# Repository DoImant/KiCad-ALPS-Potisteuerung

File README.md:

# ALPS potentiometer control

Circuit for controlling an ALPS motor potentiometer with the help of an IR remote\
control. This circuit can be used to control the volume of an amplifier.

## Circuit diagram as PDF file

[Sheet](https://github.com/DoImant/Stuff/blob/main/ALPS-Drehpoti/ALPS-Potisteuerung.pdf)

## The PCB

## Software

The software for the Atmega88P can be found here: https://github.com/DoImant/ATmega88-ALPS-Motorpoti

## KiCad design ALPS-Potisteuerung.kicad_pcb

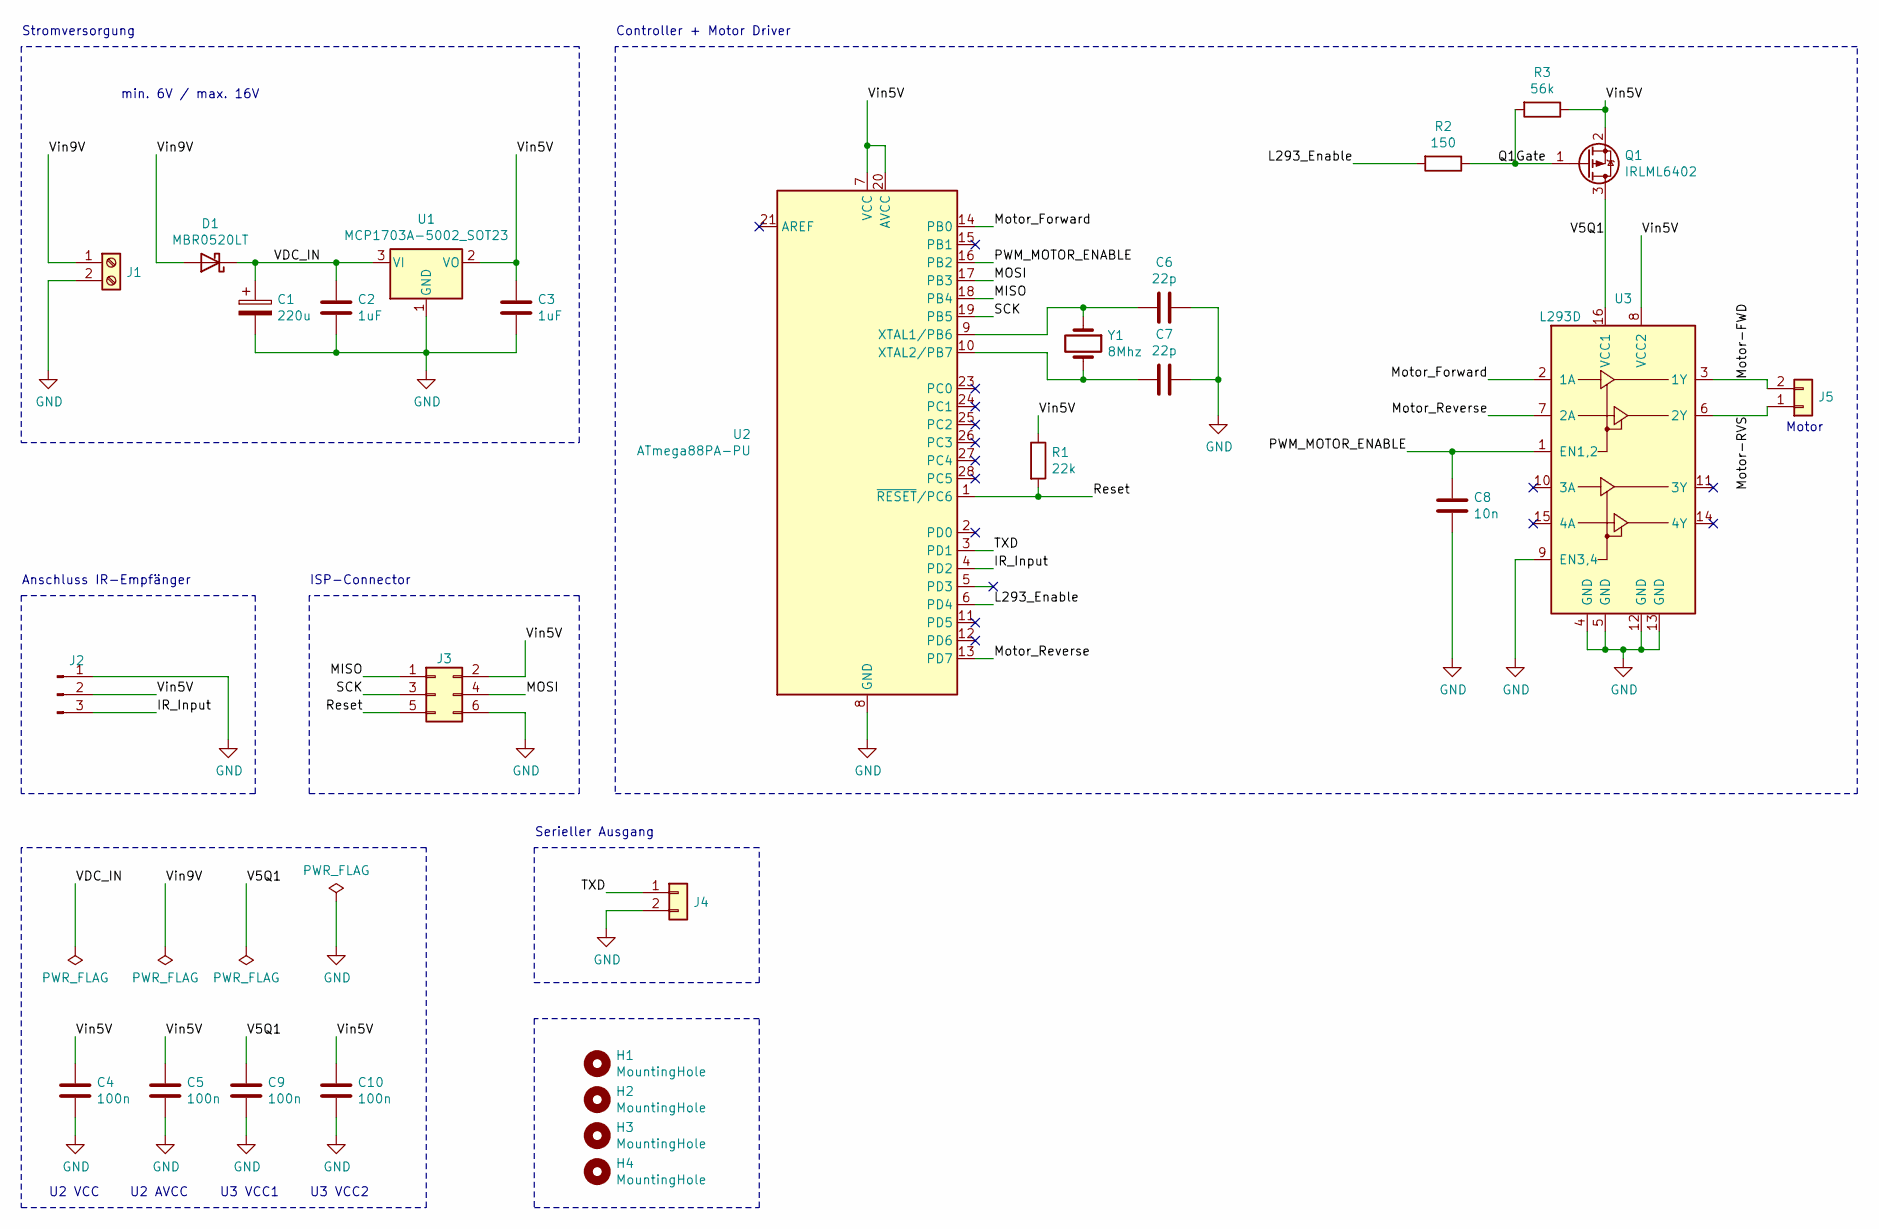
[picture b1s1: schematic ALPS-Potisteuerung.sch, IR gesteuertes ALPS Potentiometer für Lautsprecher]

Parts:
C1: 220u; CP_Elec_6.3x5.8
C2, C3: 1uF; C_1206_3216Metric_Pad1.33x1.80mm_HandSolder
C4, C5, C9, C10: 100n; C_1206_3216Metric_Pad1.33x1.80mm_HandSolder
C6, C7: 22p; C_Disc_D3.0mm_W1.6mm_P2.50mm
C8: 10n; C_1206_3216Metric_Pad1.33x1.80mm_HandSolder
D1: MBR0520LT; D_SOD-123
H1, H2, H3, H4: MountingHole; MountingHole_3.2mm_M3_DIN965_Pad
J1: Conn_01x02; TerminalBlock_RND_205-00232_1x02_P5.08mm_Horizontal
J2: Conn_01x03_Male; JST_XH_B3B-XH-A_1x03_P2.50mm_Vertical
J3: Conn_02x03_Odd_Even; IDC-Header_2x03_P2.54mm_Vertical
J4: Conn_01x02; PinHeader_1x02_P2.54mm_Vertical
J5: Conn_01x02; JST_XH_B2B-XH-A_1x02_P2.50mm_Vertical
Q1: IRLML6402; SOT-23
R1: 22k; R_1206_3216Metric_Pad1.30x1.75mm_HandSolder
R2: 150; R_1206_3216Metric_Pad1.30x1.75mm_HandSolder
R3: 56k; R_1206_3216Metric_Pad1.30x1.75mm_HandSolder
U1: MCP1703A-5002_SOT23; SOT-23
U2: ATmega88PA-PU; DIP-28_W7.62mm
U3: L293D; DIP-16_W7.62mm
Y1: 8Mhz; Crystal_HC49-4H_Vertical

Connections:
/IR_Input: J2.3, U2.4 (PD2)
/L293_Enable: R2.2, U2.6 (PD4)
/MISO: J3.1, U2.18 (PB4)
/MOSI: J3.4, U2.17 (PB3)
/Motor-FWD: J5.2, U3.3 (1Y)
/Motor-RVS: J5.1, U3.6 (2Y)
/Motor_Forward: U2.14 (PB0), U3.2 (1A)
/Motor_Reverse: U2.13 (PD7), U3.7 (2A)
/PWM_MOTOR_ENABLE: C8.1, U2.16 (PB2), U3.1 (EN1,2)
/Q1Gate: Q1.1 (G), R2.1, R3.2
/Reset: J3.5, R1.2, U2.1 (~RESET~/PC6)
/SCK: J3.3, U2.19 (PB5)
/TXD: J4.1, U2.3 (PD1)
/V5Q1: C9.1, Q1.3 (D), U3.16 (VCC1)
/VDC_IN: C1.1, C2.1, D1.1 (K), U1.3 (VI)
/Vin5V: C3.1, C4.1, C5.1, C10.1, J2.2, J3.2, Q1.2 (S), R1.1, R3.1, U1.2 (VO), U2.7 (VCC), U2.20 (AVCC), U3.8 (VCC2)
/Vin9V: D1.2 (A), J1.1
GND: C1.2, C2.2, C3.2, C4.2, C5.2, C6.1, C7.1, C8.2, C9.2, C10.2, J1.2, J2.1, J3.6, J4.2, U1.1 (GND), U2.8 (GND), U2.22 (GND), U3.4 (GND), U3.5 (GND), U3.9 (EN3,4), U3.12 (GND), U3.13 (GND)
unnamed: C6.2, U2.9 (XTAL1/PB6), Y1.1
unnamed: C7.2, U2.10 (XTAL2/PB7), Y1.2

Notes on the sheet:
Motor
min. 6V / max. 16V
Anschluss IR-Empfänger
Stromversorgung
ISP-Connector
Controller + Motor Driver
Serieller Ausgang
U2 VCC
U2 AVCC
U3 VCC1
U3 VCC2

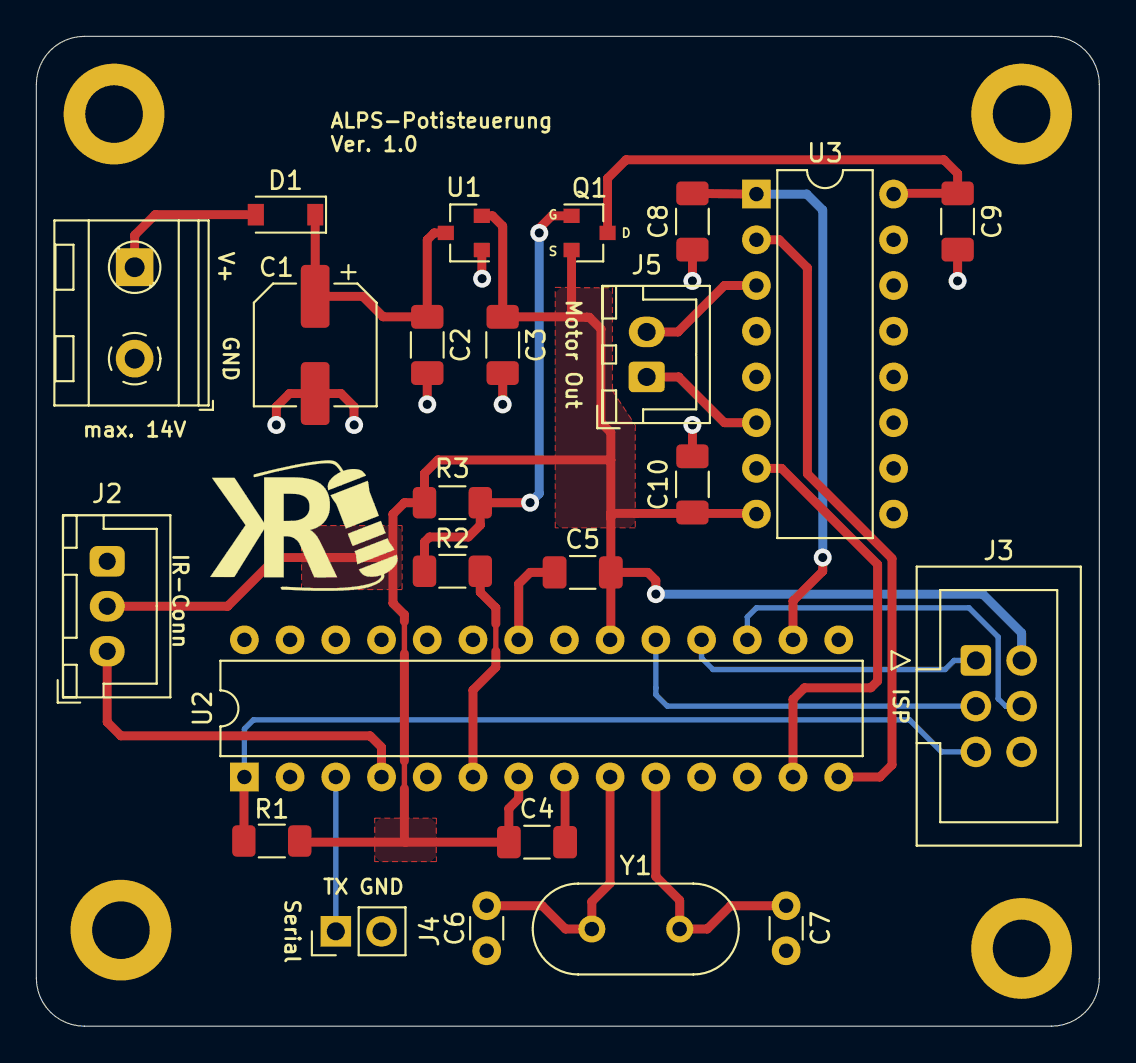
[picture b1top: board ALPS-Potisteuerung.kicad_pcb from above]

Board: 2 copper layers, 59.1 x 55.0 mm, 28 parts (0 on the bottom side), 20 nets.

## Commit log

2021-12-05 Adaptation Readme
2021-12-05 Readme changed
